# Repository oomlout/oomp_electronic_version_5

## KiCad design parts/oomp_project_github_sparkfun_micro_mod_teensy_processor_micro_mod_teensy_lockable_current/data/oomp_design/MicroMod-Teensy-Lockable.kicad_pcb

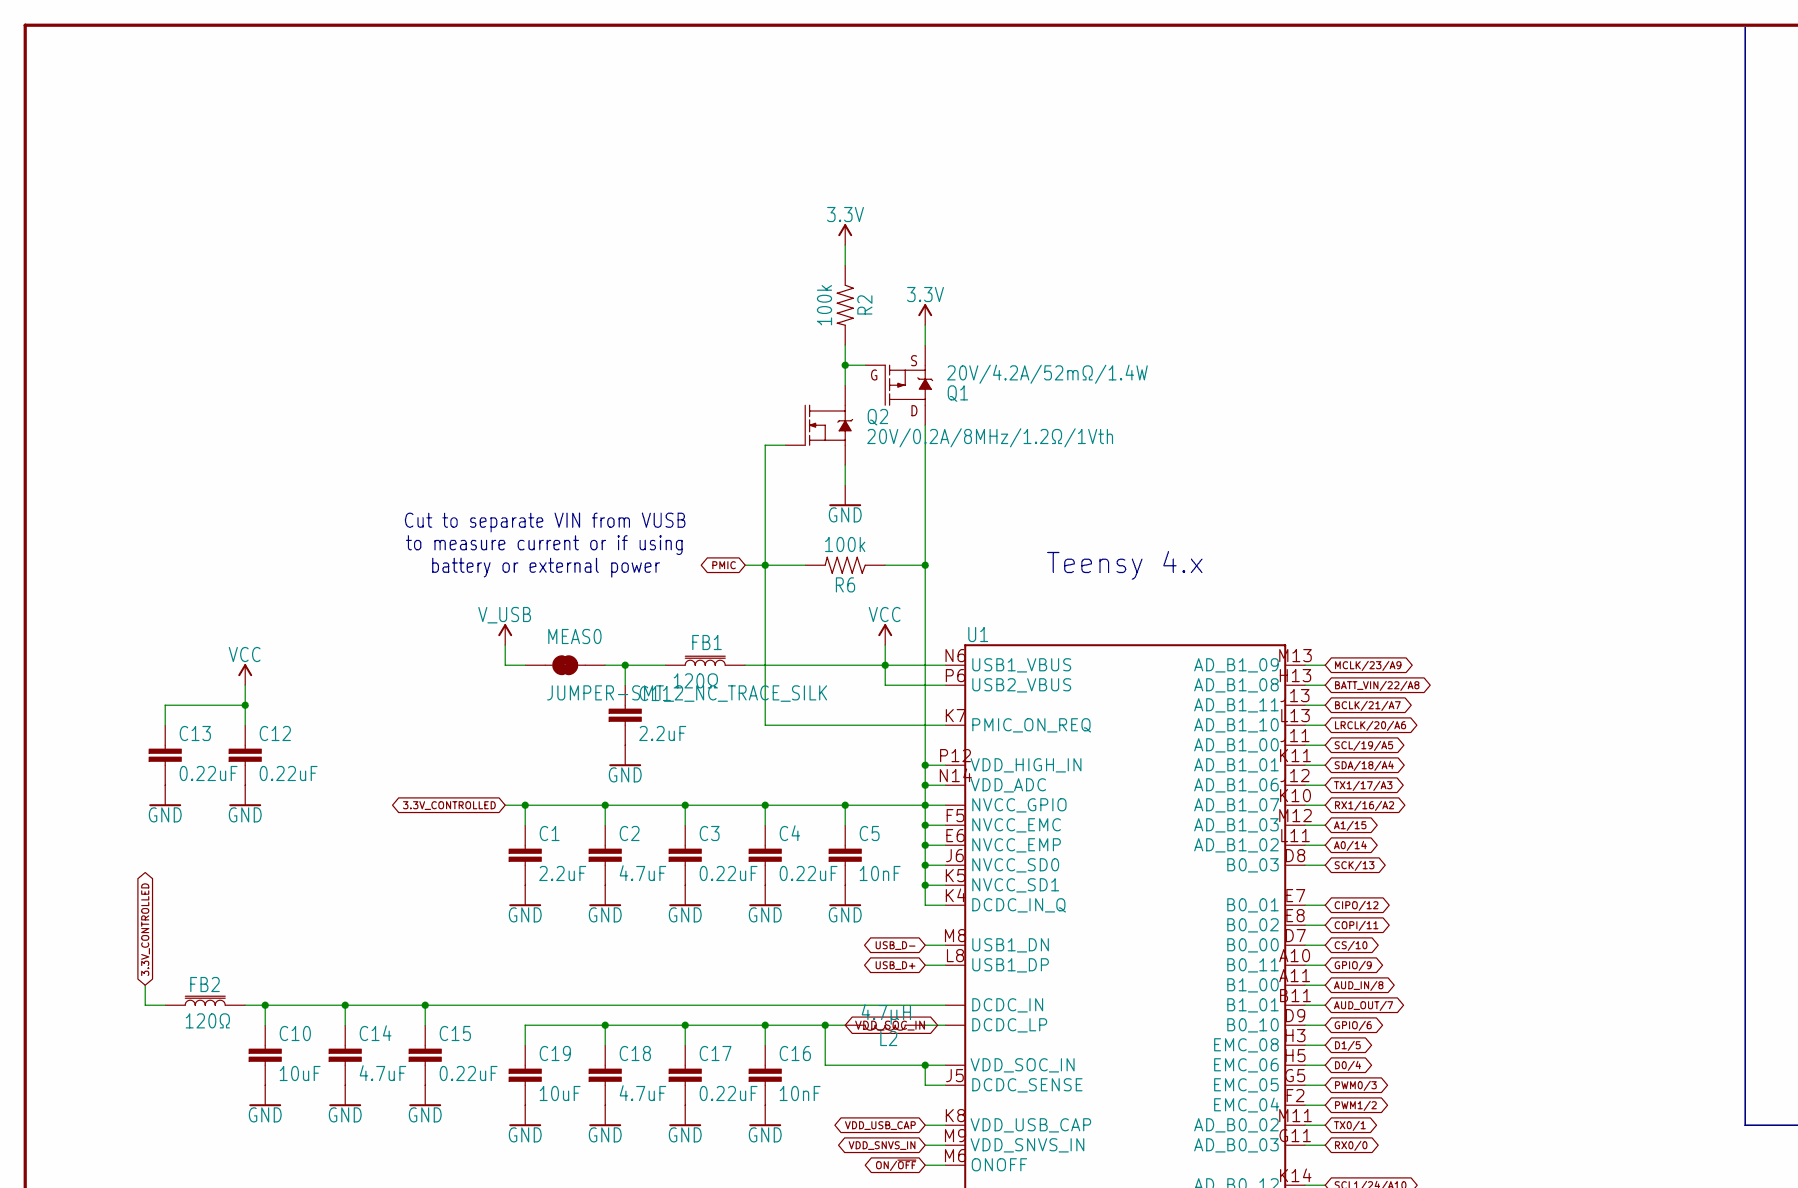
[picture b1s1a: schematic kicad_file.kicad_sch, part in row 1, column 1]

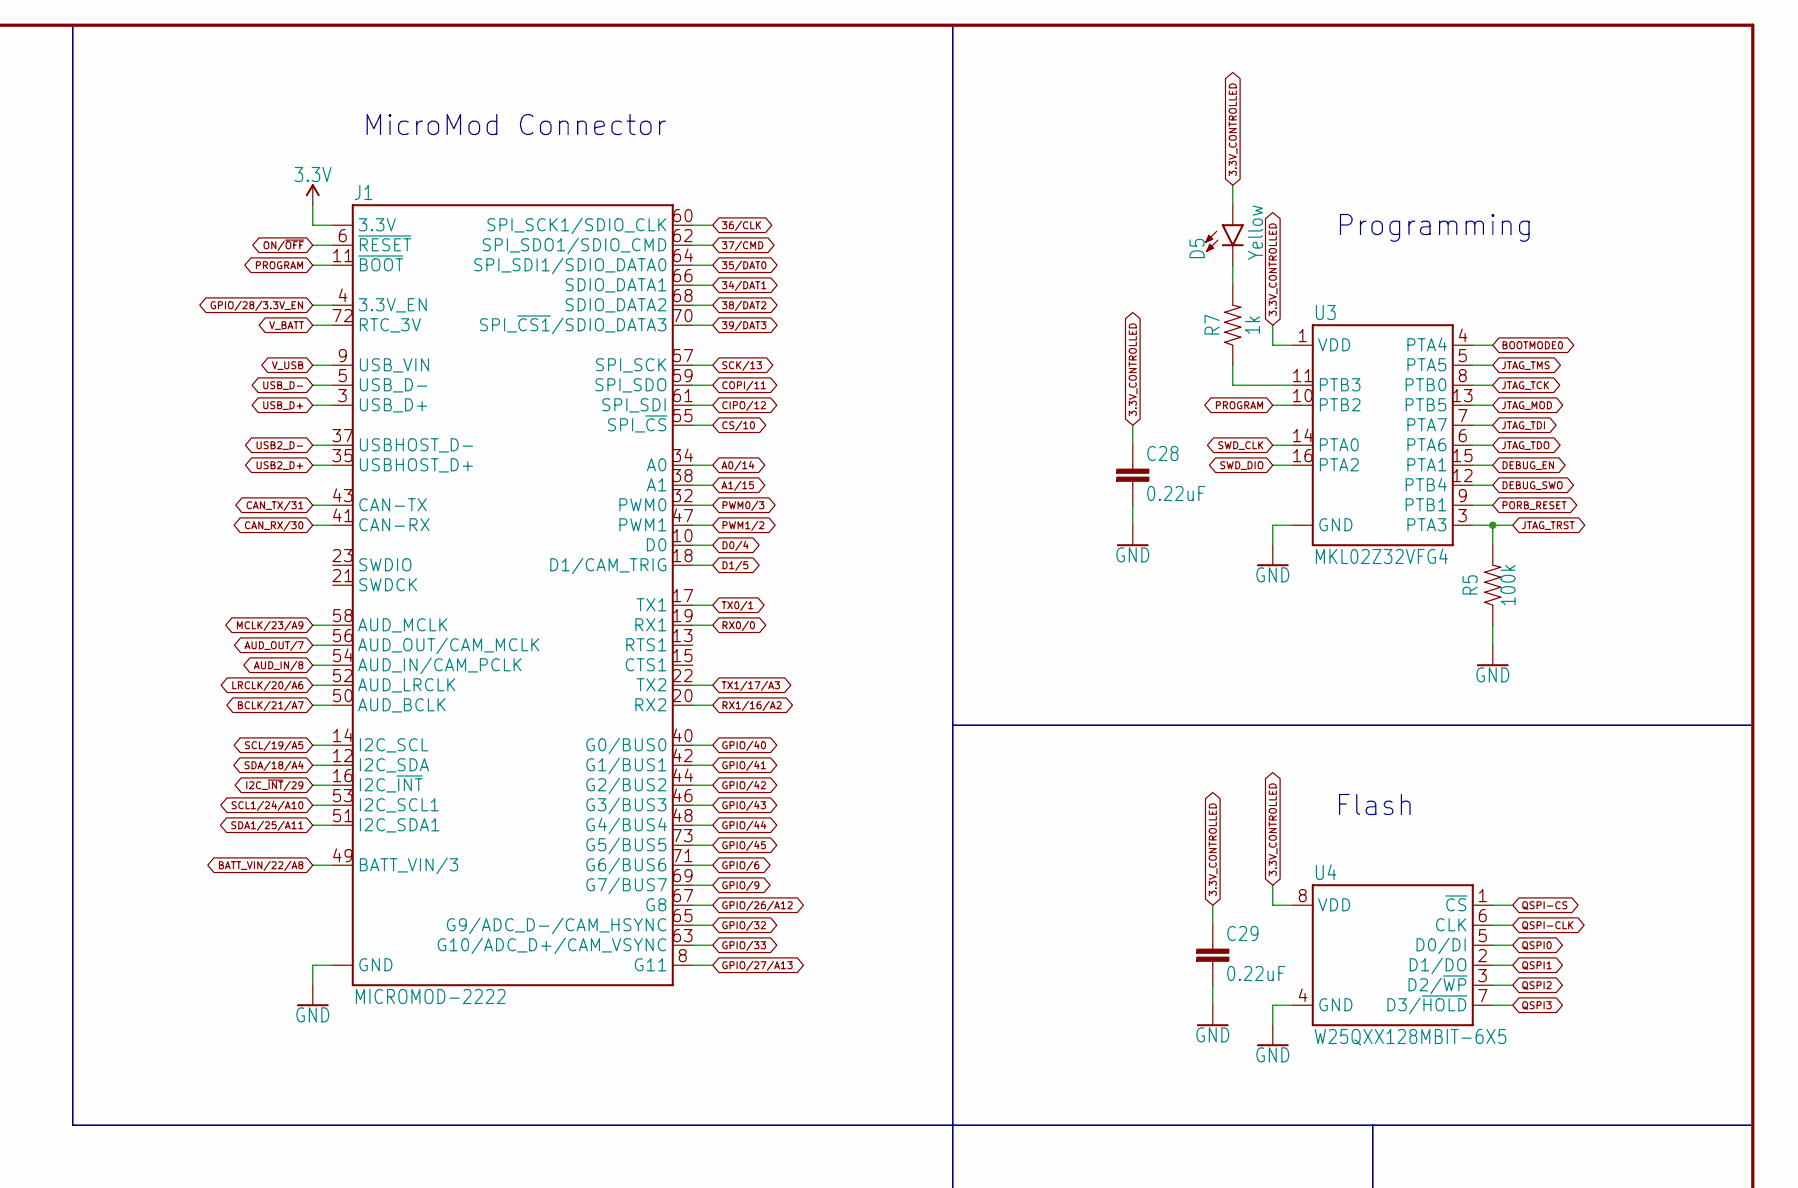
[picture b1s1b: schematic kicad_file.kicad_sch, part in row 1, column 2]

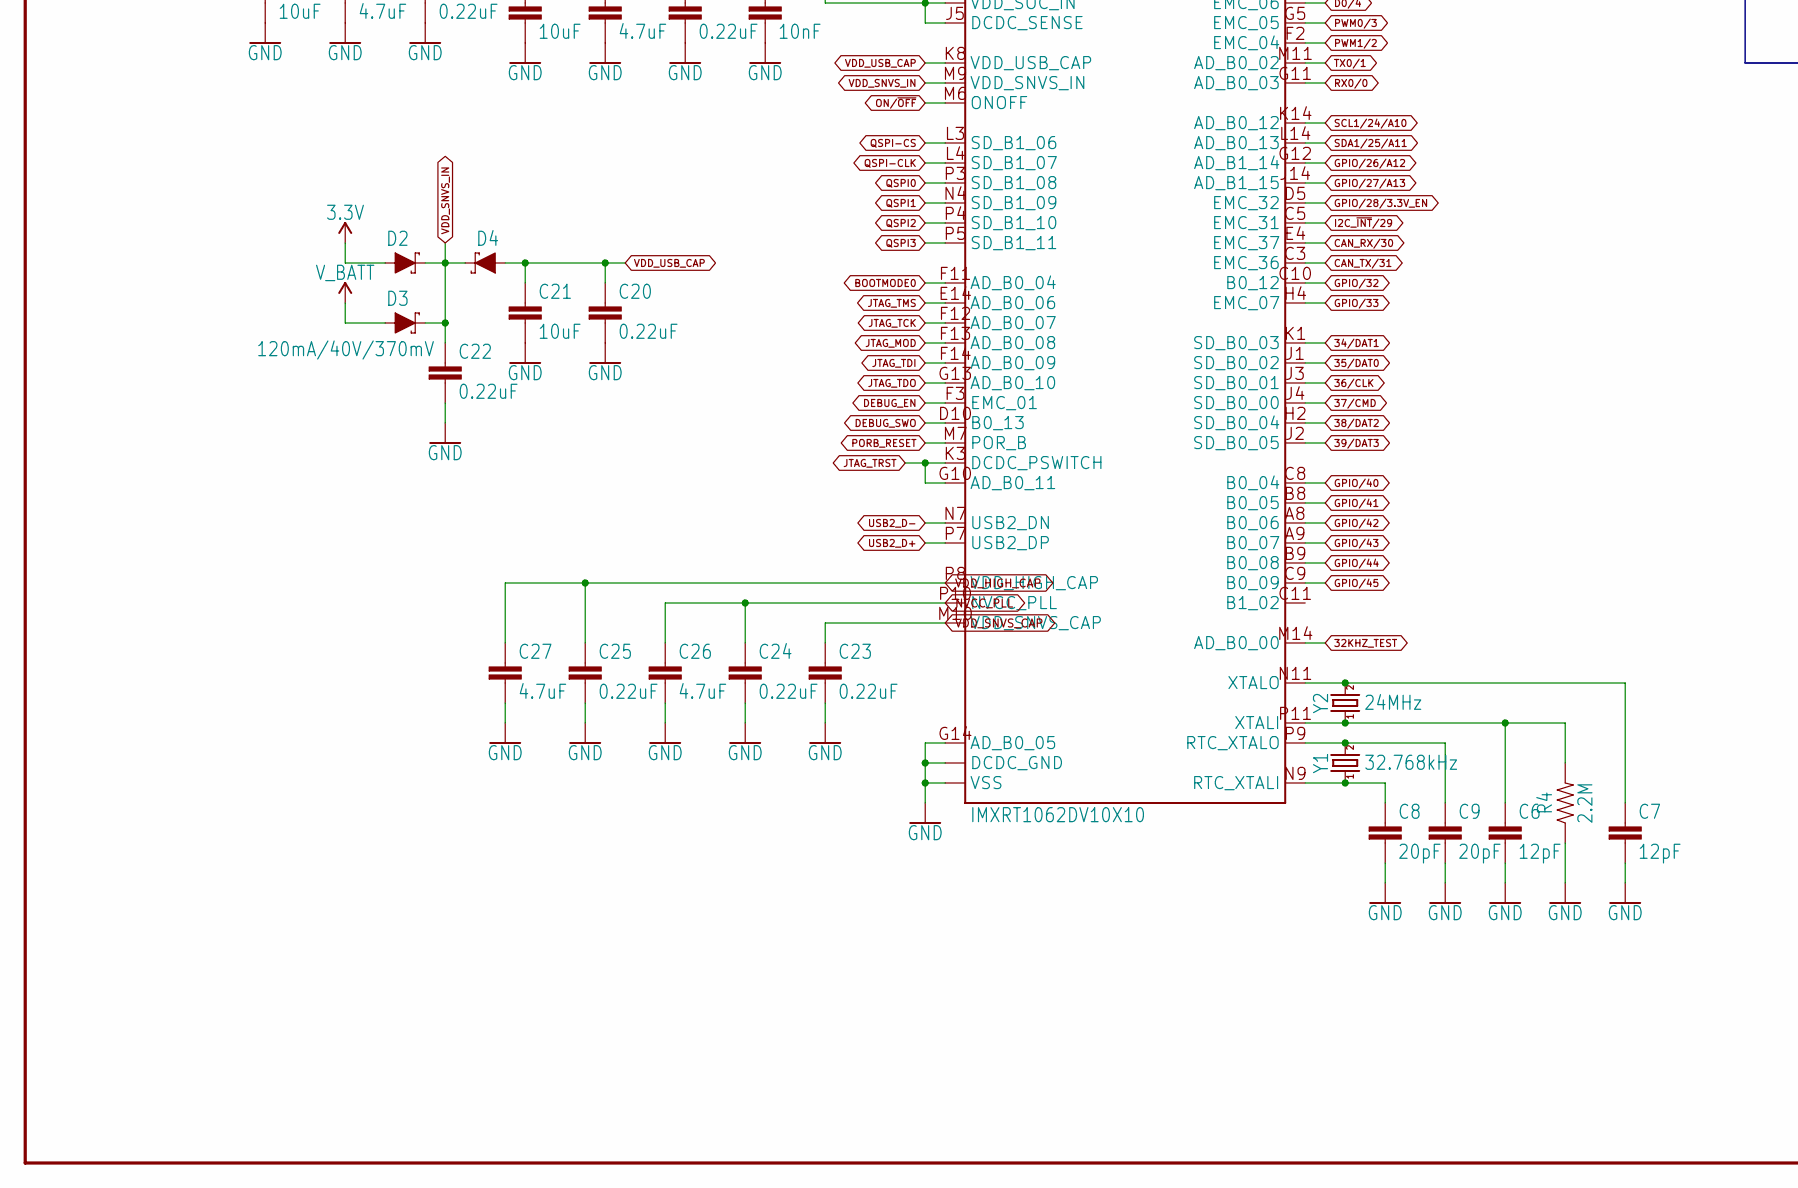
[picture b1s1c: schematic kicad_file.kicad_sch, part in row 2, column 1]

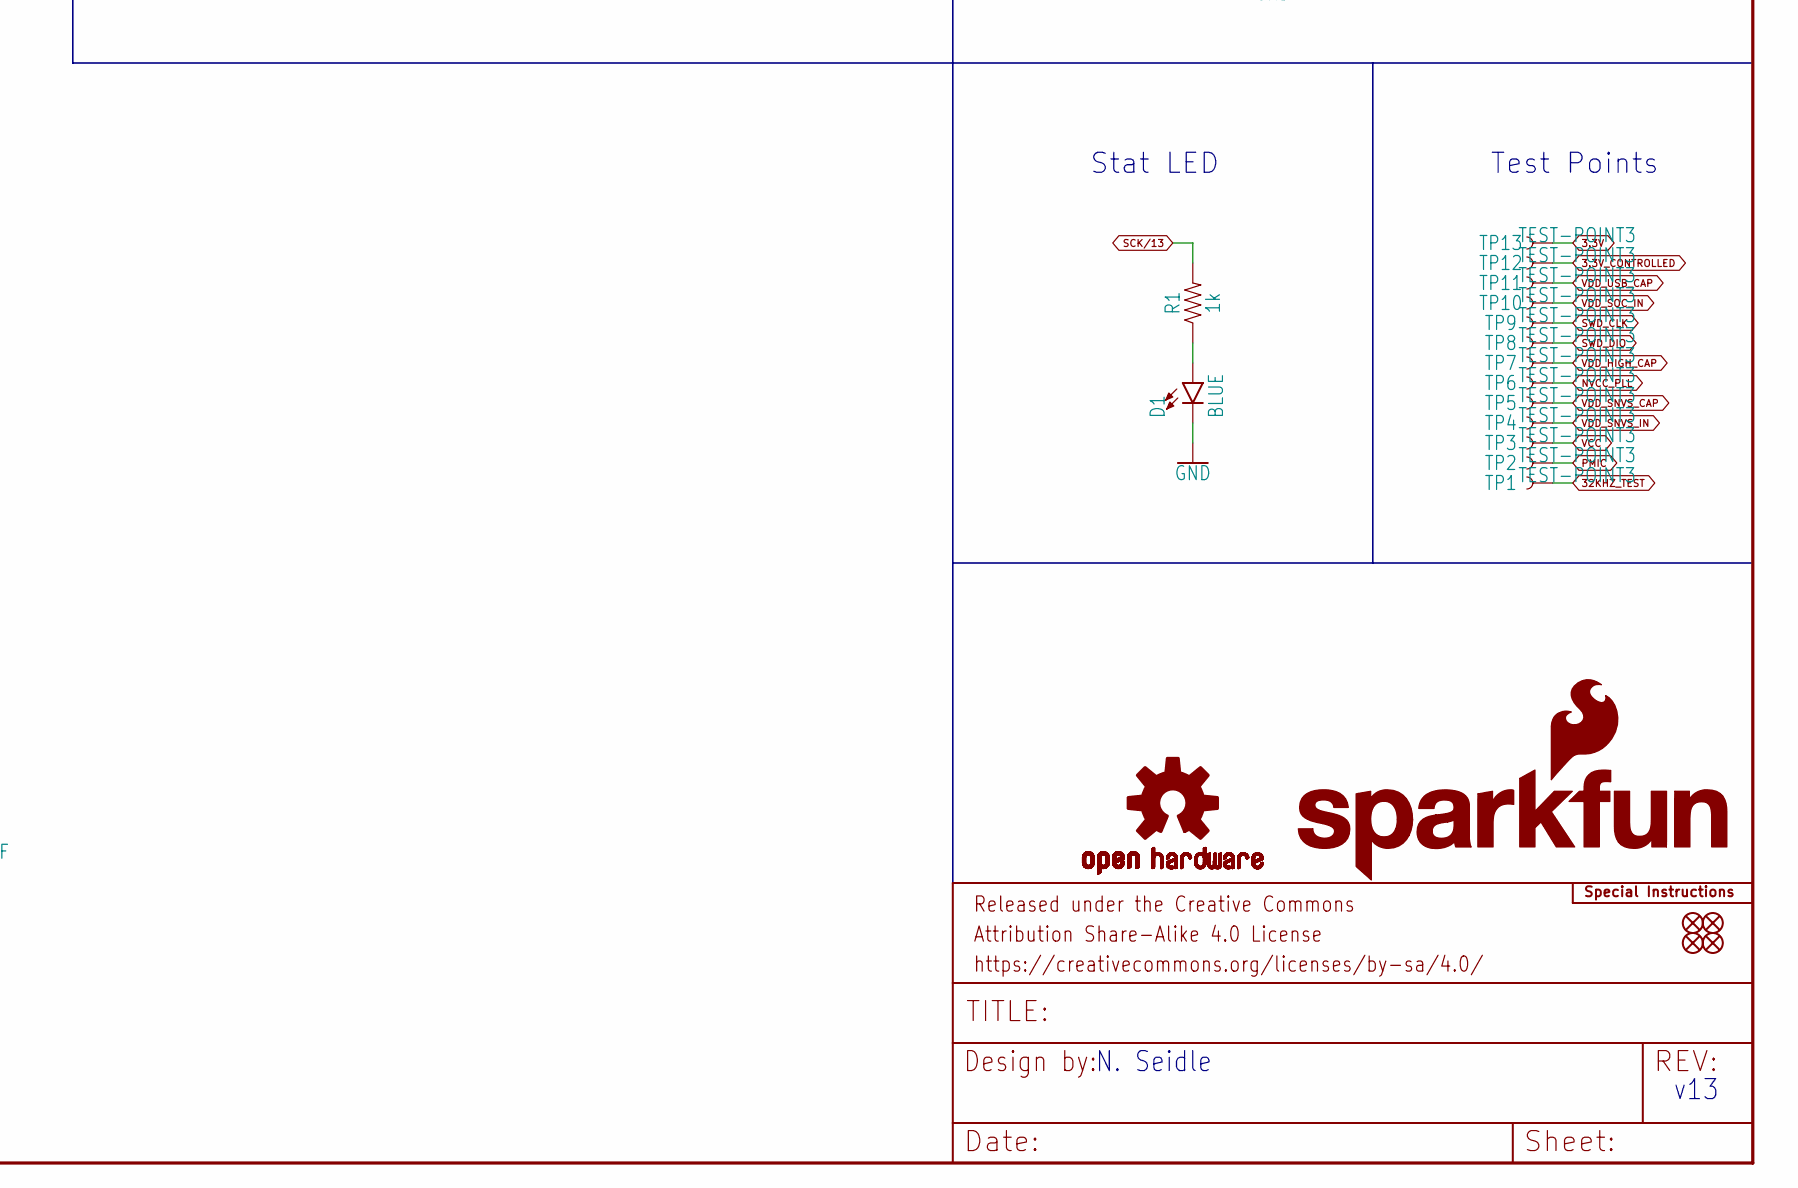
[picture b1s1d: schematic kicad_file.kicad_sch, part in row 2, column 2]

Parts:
C1, C11: 2.2uF; 0402-TIGHT
C2, C14, C18, C26, C27: 4.7uF; 0402-TIGHT
C3, C4, C12, C13, C15, C17, C20, C22, C23, C24, C25, C28, C29: 0.22uF; 0402-TIGHT
C5, C16: 10nF; 0402-TIGHT
C6, C7: 12pF; 0402-TIGHT
C8, C9: 20pF; 0402-TIGHT
C10, C19, C21: 10uF; 0402-TIGHT
D1: BLUE; LED-0603
D2, D3, D4: 120mA/40V/370mV; SOD-523
D5: Yellow; LED-0603
FB1, FB2: 120Ω; 0402-TIGHT
FD1, FD2, FD3, FD4: FIDUCIALUFIDUCIAL; FIDUCIAL-MICRO
FRAME1: FRAME-LEDGER; CREATIVE_COMMONS
J1: MICROMOD-2222; M.2-CARD-E-22
L2: 4.7μH; 1008(2520)
LOGO1: SFE_LOGO_NAME_FLAME.1_INCH; SFE_LOGO_NAME_FLAME_.1
LOGO2: OSHW-LOGONO_SILK; DUMMY
LOGO3: SPECIAL_INSTRUCTIONS-ORDERING; ORDERING_INSTRUCTIONS
MEAS0: JUMPER-SMT_2_NC_TRACE_SILK; SMT-JUMPER_2_NC_TRACE_SILK
Q1: 20V/4.2A/52mΩ/1.4W; SOT23-3
Q2: 20V/0.2A/8MHz/1.2Ω/1Vth; SOT-416FL
R1, R7: 1k; 0402-TIGHT
R2, R5, R6: 100k; 0402-TIGHT
R4: 2.2M; 0402-TIGHT
TP1, TP2, TP3, TP4, TP5, TP6, TP7, TP8, TP9, TP10, TP11, TP12, TP13: TEST-POINT3; PAD.03X.03
U1: IMXRT1062DV10X10; IMXRT1062
U3: MKL02Z32VFG4; QFN-16
U4: W25QXX128MBIT-6X5; WSON-8-6X5-SKINNY_CENTERPAD
Y1: 32.768kHz; CRYSTAL-SMD-3.2X1.5MM
Y2: 24MHz; CRYSTAL-SMD-2.0X1.6MM

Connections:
3.3V: D2.A, J1.2 (3.3V), J1.74 (3.3V), Q1.2 (S), R2.1, TP13.P$1
3.3V_CONTROLLED: C1.1, C2.1, C3.1, C4.1, C5.1, C28.1, C29.1, D5.A, FB2.1, Q1.3 (D), R6.1, TP12.P$1, U1.E6 (NVCC_EMP), U1.E9 (NVCC_GPIO), U1.F5 (NVCC_EMC), U1.F10 (NVCC_GPIO), U1.J6 (NVCC_SD0), U1.J10 (NVCC_GPIO), U1.K4 (DCDC_IN_Q), U1.K5 (NVCC_SD1), U1.N14 (VDD_ADC), U1.P12 (VDD_HIGH_IN), U3.1 (VDD), U4.8 (VDD)
24MHZ_1: C7.1, U1.N11 (XTALO), Y2.3 (2)
24MHZ_2: C6.1, R4.2, U1.P11 (XTALI), Y2.1
32KHZ_1: C8.1, U1.N9 (RTC_XTALI), Y1.P$1 (1)
32KHZ_2: C9.1, U1.P9 (RTC_XTALO), Y1.P$2 (2)
32KHZ_TEST: TP1.P$1, U1.M14 (AD_B0_00)
34/DAT1: J1.66 (SDIO_DATA1), U1.K1 (SD_B0_03)
35/DAT0: J1.64 (SPI_SDI1/SDIO_DATA0), U1.J1 (SD_B0_02)
36/CLK: J1.60 (SPI_SCK1/SDIO_CLK), U1.J3 (SD_B0_01)
37/CMD: J1.62 (SPI_SDO1/SDIO_CMD), U1.J4 (SD_B0_00)
38/DAT2: J1.68 (SDIO_DATA2), U1.H2 (SD_B0_04)
39/DAT3: J1.70 (SPI_~CS1/SDIO_DATA3), U1.J2 (SD_B0_05)
A0/14: J1.34 (A0), U1.L11 (AD_B1_02)
A1/15: J1.38 (A1), U1.M12 (AD_B1_03)
AUD_IN/8: J1.54 (AUD_IN/CAM_PCLK), U1.A11 (B1_00)
AUD_OUT/7: J1.56 (AUD_OUT/CAM_MCLK), U1.B11 (B1_01)
BATT_VIN/22/A8: J1.49 (BATT_VIN/3), U1.H13 (AD_B1_08)
BCLK/21/A7: J1.50 (AUD_BCLK), U1.J13 (AD_B1_11)
BOOTMODE0: U1.F11 (AD_B0_04), U3.4 (PTA4)
CAN_RX/30: J1.41 (CAN-RX), U1.E4 (EMC_37)
CAN_TX/31: J1.43 (CAN-TX), U1.C3 (EMC_36)
CIPO/12: J1.61 (SPI_SDI), U1.E7 (B0_01)
COPI/11: J1.59 (SPI_SDO), U1.E8 (B0_02)
CS/10: J1.55 (SPI_~CS), U1.D7 (B0_00)
D0/4: J1.10 (D0), U1.H5 (EMC_06)
D1/5: J1.18 (D1/CAM_TRIG), U1.H3 (EMC_08)
DCDC_IN: C10.1, C14.1, C15.1, FB2.2, U1.L1 (DCDC_IN), U1.L2 (DCDC_IN)
DCDC_LP: L2.1, U1.M1 (DCDC_LP), U1.M2 (DCDC_LP)
DEBUG_EN: U1.F3 (EMC_01), U3.15 (PTA1)
DEBUG_SWO: U1.D10 (B0_13), U3.12 (PTB4)
GND: C1.2, C2.2, C3.2, C4.2, C5.2, C6.2, C7.2, C8.2, C9.2, C10.2, C11.2, C12.2, C13.2, C14.2, C15.2, C16.2, C17.2, C18.2, C19.2, C20.2, C21.2, C22.2, C23.2, C24.2, C25.2, C26.2, C27.2, C28.2, C29.2, D1.C, J1.1 (GND), J1.7 (GND), J1.33 (GND), J1.36 (GND), J1.39 (GND), J1.45 (GND), J1.75 (GND), J1.GND1 (GND), J1.GND2 (GND), J1.GND3 (GND), Q2.2 (S), R4.1, R5.1, U1.A1 (VSS), U1.A14 (VSS), U1.B5 (VSS), U1.B10 (VSS), U1.E2 (VSS), U1.E13 (VSS), U1.G7 (VSS), U1.G8 (VSS), U1.G14 (AD_B0_05), U1.H7 (VSS), U1.H8 (VSS), U1.J7 (VSS), U1.J8 (VSS), U1.K2 (VSS), U1.K6 (VSS), U1.K9 (VSS), U1.K13 (VSS), U1.L9 (VSS), U1.N1 (DCDC_GND), U1.N2 (DCDC_GND), U1.N5 (VSS), U1.N8 (VSS), U1.P1 (VSS), U1.P14 (VSS), U3.2 (GND), U3.17 (GND), U4.4 (GND)
GPIO/6: J1.71 (G6/BUS6), U1.D9 (B0_10)
GPIO/9: J1.69 (G7/BUS7), U1.A10 (B0_11)
GPIO/26/A12: J1.67 (G8), U1.G12 (AD_B1_14)
GPIO/27/A13: J1.8 (G11), U1.J14 (AD_B1_15)
GPIO/28/3.3V_EN: J1.4 (3.3V_EN), U1.D5 (EMC_32)
GPIO/32: J1.65 (G9/ADC_D-/CAM_HSYNC), U1.C10 (B0_12)
GPIO/33: J1.63 (G10/ADC_D+/CAM_VSYNC), U1.H4 (EMC_07)
GPIO/40: J1.40 (G0/BUS0), U1.C8 (B0_04)
GPIO/41: J1.42 (G1/BUS1), U1.B8 (B0_05)
GPIO/42: J1.44 (G2/BUS2), U1.A8 (B0_06)
GPIO/43: J1.46 (G3/BUS3), U1.A9 (B0_07)
GPIO/44: J1.48 (G4/BUS4), U1.B9 (B0_08)
GPIO/45: J1.73 (G5/BUS5), U1.C9 (B0_09)
I2C_~INT/29: J1.16 (I2C_~INT), U1.C5 (EMC_31)
JTAG_MOD: U1.F13 (AD_B0_08), U3.13 (PTB5)
JTAG_TCK: U1.F12 (AD_B0_07), U3.8 (PTB0)
JTAG_TDI: U1.F14 (AD_B0_09), U3.7 (PTA7)
JTAG_TDO: U1.G13 (AD_B0_10), U3.6 (PTA6)
JTAG_TMS: U1.E14 (AD_B0_06), U3.5 (PTA5)
JTAG_TRST: R5.2, U1.G10 (AD_B0_11), U1.K3 (DCDC_PSWITCH), U3.3 (PTA3)
LRCLK/20/A6: J1.52 (AUD_LRCLK), U1.L13 (AD_B1_10)
MCLK/23/A9: J1.58 (AUD_MCLK), U1.M13 (AD_B1_09)
unnamed: D1.A, R1.1
unnamed: Q1.1 (G), Q2.3 (D), R2.2
unnamed: C11.1, FB1.1, MEAS0.2
unnamed: R7.1, U3.11 (PTB3)
unnamed: D5.C, R7.2
NVCC_PLL: C24.1, C26.1, TP6.P$1, U1.P10 (NVCC_PLL)
ON/~OFF: J1.6 (~RESET), U1.M6 (ONOFF)
PMIC: Q2.1 (G), R6.2, TP2.P$1, U1.K7 (PMIC_ON_REQ)
PORB_RESET: U1.M7 (POR_B), U3.9 (PTB1)
PROGRAM: J1.11 (~BOOT), U3.10 (PTB2)
PWM0/3: J1.32 (PWM0), U1.G5 (EMC_05)
PWM1/2: J1.47 (PWM1), U1.F2 (EMC_04)
QSPI0: U1.P3 (SD_B1_08), U4.5 (D0/DI)
QSPI1: U1.N4 (SD_B1_09), U4.2 (D1/DO)
QSPI2: U1.P4 (SD_B1_10), U4.3 (D2/~WP)
QSPI3: U1.P5 (SD_B1_11), U4.7 (D3/~HOLD)
QSPI-CLK: U1.L4 (SD_B1_07), U4.6 (CLK)
QSPI-CS: U1.L3 (SD_B1_06), U4.1 (~CS)
RX0/0: J1.19 (RX1), U1.G11 (AD_B0_03)
RX1/16/A2: J1.20 (RX2), U1.K10 (AD_B1_07)
SCK/13: J1.57 (SPI_SCK), R1.2, U1.D8 (B0_03)
SCL1/24/A10: J1.53 (I2C_SCL1), U1.K14 (AD_B0_12)
SCL/19/A5: J1.14 (I2C_SCL), U1.J11 (AD_B1_00)
SDA1/25/A11: J1.51 (I2C_SDA1), U1.L14 (AD_B0_13)
SDA/18/A4: J1.12 (I2C_SDA), U1.K11 (AD_B1_01)
SWD_CLK: TP9.P$1, U3.14 (PTA0)
SWD_DIO: TP8.P$1, U3.16 (PTA2)
TX0/1: J1.17 (TX1), U1.M11 (AD_B0_02)
TX1/17/A3: J1.22 (TX2), U1.J12 (AD_B1_06)
USB2_D+: J1.35 (USBHOST_D+), U1.P7 (USB2_DP)
USB2_D-: J1.37 (USBHOST_D-), U1.N7 (USB2_DN)
USB_D+: J1.3 (USB_D+), U1.L8 (USB1_DP)
USB_D-: J1.5 (USB_D-), U1.M8 (USB1_DN)
VCC: C12.1, C13.1, FB1.2, TP3.P$1, U1.N6 (USB1_VBUS), U1.P6 (USB2_VBUS)
VDD_HIGH_CAP: C25.1, C27.1, TP7.P$1, U1.P8 (VDD_HIGH_CAP)
VDD_SNVS_CAP: C23.1, TP5.P$1, U1.M10 (VDD_SNVS_CAP)
VDD_SNVS_IN: C22.1, D2.C, D3.C, D4.C, TP4.P$1, U1.M9 (VDD_SNVS_IN)
VDD_SOC_IN: C16.1, C17.1, C18.1, C19.1, L2.2, TP10.P$1, U1.F6 (VDD_SOC_IN), U1.F7 (VDD_SOC_IN), U1.F8 (VDD_SOC_IN), U1.F9 (VDD_SOC_IN), U1.G6 (VDD_SOC_IN), U1.G9 (VDD_SOC_IN), U1.H6 (VDD_SOC_IN), U1.H9 (VDD_SOC_IN), U1.J5 (DCDC_SENSE), U1.J9 (VDD_SOC_IN)
VDD_USB_CAP: C20.1, C21.1, D4.A, TP11.P$1, U1.K8 (VDD_USB_CAP)
V_BATT: D3.A, J1.72 (RTC_3V)
V_USB: J1.9 (USB_VIN), MEAS0.1

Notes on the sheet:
Flash
N. Seidle
Teensy 4.x
Test Points
v13
Stat LED
Cut to separate VIN from VUSB to measure current or if using battery or external power
MicroMod Connector
Programming

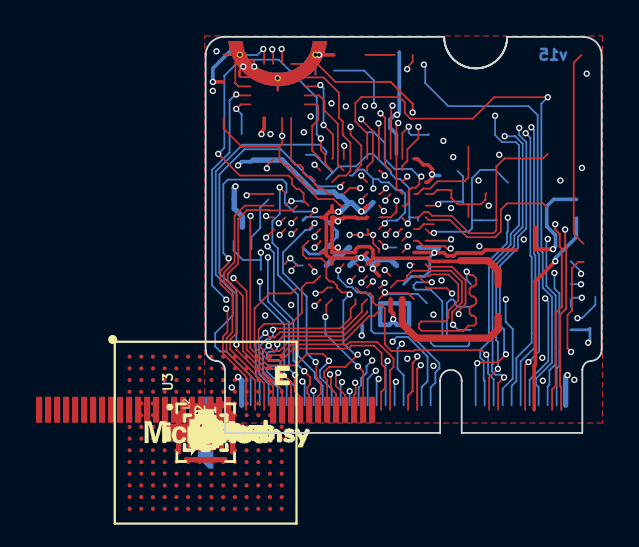
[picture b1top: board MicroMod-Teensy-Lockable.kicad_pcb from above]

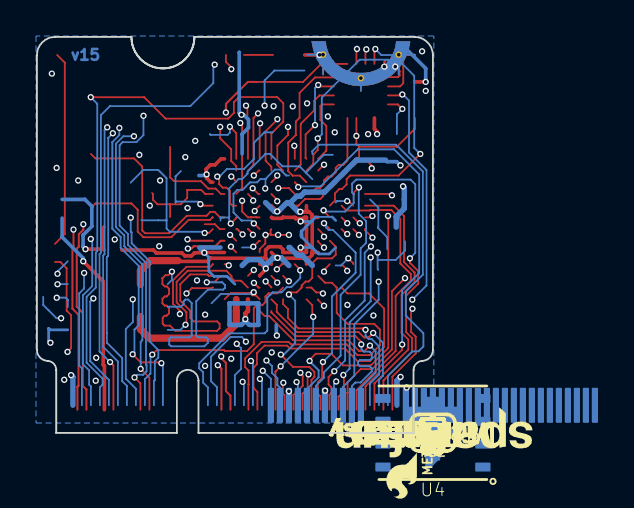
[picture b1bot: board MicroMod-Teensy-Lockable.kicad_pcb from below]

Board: 4 copper layers, 22.0 x 22.0 mm, 84 parts (53 on the bottom side), 95 nets.

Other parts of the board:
U$1, U$3: TEENSY2
U$4: MICROMOD_MI_LOGO_.35
U$6: SFE_LOGO_FLAME_.1
U$7, U$11: MICROMOD_LOGO_.3
U$8: MEAS2
U$9: PROG0
U$10: STAT1
U$16, U$17: LOCKED4#PNG

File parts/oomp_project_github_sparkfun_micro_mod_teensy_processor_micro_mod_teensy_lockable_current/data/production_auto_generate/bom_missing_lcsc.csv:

Designator,Comment,Footprint,OOMP ID,Reason
C3,0.22uF,MicroMod-Teensy-Lockable-import-fps:0402-TIGHT,,No verified LCSC part number
C4,0.22uF,MicroMod-Teensy-Lockable-import-fps:0402-TIGHT,,No verified LCSC part number
C6,12pF,MicroMod-Teensy-Lockable-import-fps:0402-TIGHT,,No verified LCSC part number
C7,12pF,MicroMod-Teensy-Lockable-import-fps:0402-TIGHT,,No verified LCSC part number
C8,20pF,MicroMod-Teensy-Lockable-import-fps:0402-TIGHT,,No verified LCSC part number
C9,20pF,MicroMod-Teensy-Lockable-import-fps:0402-TIGHT,,No verified LCSC part number
C12,0.22uF,MicroMod-Teensy-Lockable-import-fps:0402-TIGHT,,No verified LCSC part number
C13,0.22uF,MicroMod-Teensy-Lockable-import-fps:0402-TIGHT,,No verified LCSC part number
C15,0.22uF,MicroMod-Teensy-Lockable-import-fps:0402-TIGHT,,No verified LCSC part number
C17,0.22uF,MicroMod-Teensy-Lockable-import-fps:0402-TIGHT,,No verified LCSC part number
C20,0.22uF,MicroMod-Teensy-Lockable-import-fps:0402-TIGHT,,No verified LCSC part number
C22,0.22uF,MicroMod-Teensy-Lockable-import-fps:0402-TIGHT,,No verified LCSC part number
C23,0.22uF,MicroMod-Teensy-Lockable-import-fps:0402-TIGHT,,No verified LCSC part number
C24,0.22uF,MicroMod-Teensy-Lockable-import-fps:0402-TIGHT,,No verified LCSC part number
C25,0.22uF,MicroMod-Teensy-Lockable-import-fps:0402-TIGHT,,No verified LCSC part number
C28,0.22uF,MicroMod-Teensy-Lockable-import-fps:0402-TIGHT,,No verified LCSC part number
C29,0.22uF,MicroMod-Teensy-Lockable-import-fps:0402-TIGHT,,No verified LCSC part number
D1,BLUE,MicroMod-Teensy-Lockable-import-fps:LED-0603,electronic_led_0603_blue,No verified LCSC part number
D2,120mA/40V/370mV,MicroMod-Teensy-Lockable-import-fps:SOD-523,,No verified LCSC part number
D3,120mA/40V/370mV,MicroMod-Teensy-Lockable-import-fps:SOD-523,,No verified LCSC part number
D4,120mA/40V/370mV,MicroMod-Teensy-Lockable-import-fps:SOD-523,,No verified LCSC part number
D5,Yellow,MicroMod-Teensy-Lockable-import-fps:LED-0603,electronic_led_0603_yellow,No verified LCSC part number
FB1,120Ω,MicroMod-Teensy-Lockable-import-fps:0402-TIGHT,,No verified LCSC part number
FB2,120Ω,MicroMod-Teensy-Lockable-import-fps:0402-TIGHT,,No verified LCSC part number
FD1,FIDUCIALUFIDUCIAL,MicroMod-Teensy-Lockable-import-fps:FIDUCIAL-MICRO,,No verified LCSC part number
FD2,FIDUCIALUFIDUCIAL,MicroMod-Teensy-Lockable-import-fps:FIDUCIAL-MICRO,,No verified LCSC part number
FD3,FIDUCIALUFIDUCIAL,MicroMod-Teensy-Lockable-import-fps:FIDUCIAL-MICRO,,No verified LCSC part number
FD4,FIDUCIALUFIDUCIAL,MicroMod-Teensy-Lockable-import-fps:FIDUCIAL-MICRO,,No verified LCSC part number
FRAME1,FRAME-LEDGER,MicroMod-Teensy-Lockable-import-fps:CREATIVE_COMMONS,,No verified LCSC part number
J1,MICROMOD-2222,MicroMod-Teensy-Lockable-import-fps:M.2-CARD-E-22,,No verified LCSC part number
L2,4.7μH,MicroMod-Teensy-Lockable-import-fps:1008(2520),,No verified LCSC part number
MEAS0,,MicroMod-Teensy-Lockable-import-fps:SMT-JUMPER_2_NC_TRACE_SILK,,No verified LCSC part number
Q1,20V/4.2A/52mΩ/1.4W,MicroMod-Teensy-Lockable-import-fps:SOT23-3,,No verified LCSC part number
Q2,20V/0.2A/8MHz/1.2Ω/1Vth,MicroMod-Teensy-Lockable-import-fps:SOT-416FL,,No verified LCSC part number
TP1,,MicroMod-Teensy-Lockable-import-fps:PAD.03X.03,,No verified LCSC part number
TP2,,MicroMod-Teensy-Lockable-import-fps:PAD.03X.03,,No verified LCSC part number
TP3,,MicroMod-Teensy-Lockable-import-fps:PAD.03X.03,,No verified LCSC part number
TP4,,MicroMod-Teensy-Lockable-import-fps:PAD.03X.03,,No verified LCSC part number
TP5,,MicroMod-Teensy-Lockable-import-fps:PAD.03X.03,,No verified LCSC part number
TP6,,MicroMod-Teensy-Lockable-import-fps:PAD.03X.03,,No verified LCSC part number
TP7,,MicroMod-Teensy-Lockable-import-fps:PAD.03X.03,,No verified LCSC part number
TP8,,MicroMod-Teensy-Lockable-import-fps:PAD.03X.03,,No verified LCSC part number
TP9,,MicroMod-Teensy-Lockable-import-fps:PAD.03X.03,,No verified LCSC part number
TP10,,MicroMod-Teensy-Lockable-import-fps:PAD.03X.03,,No verified LCSC part number
TP11,,MicroMod-Teensy-Lockable-import-fps:PAD.03X.03,,No verified LCSC part number
TP12,,MicroMod-Teensy-Lockable-import-fps:PAD.03X.03,,No verified LCSC part number
TP13,,MicroMod-Teensy-Lockable-import-fps:PAD.03X.03,,No verified LCSC part number
U1,IMXRT1062DV10X10,MicroMod-Teensy-Lockable-import-fps:IMXRT1062,,No verified LCSC part number
U3,MKL02Z32VFG4,MicroMod-Teensy-Lockable-import-fps:QFN-16,,No verified LCSC part number
U4,W25QXX128MBIT-6X5,MicroMod-Teensy-Lockable-import-fps:WSON-8-6X5-SKINNY_CENTERPAD,,No verified LCSC part number
U$1,,MicroMod-Teensy-Lockable-import-fps:TEENSY2,,No verified LCSC part number
U$3,,MicroMod-Teensy-Lockable-import-fps:TEENSY2,,No verified LCSC part number
U$4,,MicroMod-Teensy-Lockable-import-fps:MICROMOD_MI_LOGO_.35,,No verified LCSC part number
U$6,,MicroMod-Teensy-Lockable-import-fps:SFE_LOGO_FLAME_.1,,No verified LCSC part number
U$7,,MicroMod-Teensy-Lockable-import-fps:MICROMOD_LOGO_.3,,No verified LCSC part number
U$8,,MicroMod-Teensy-Lockable-import-fps:MEAS2,,No verified LCSC part number
U$9,,MicroMod-Teensy-Lockable-import-fps:PROG0,,No verified LCSC part number
U$10,,MicroMod-Teensy-Lockable-import-fps:STAT1,,No verified LCSC part number
U$11,,MicroMod-Teensy-Lockable-import-fps:MICROMOD_LOGO_.3,,No verified LCSC part number
U$16,,MicroMod-Teensy-Lockable-import-fps:LOCKED4#PNG,,No verified LCSC part number
U$17,,MicroMod-Teensy-Lockable-import-fps:LOCKED4#PNG,,No verified LCSC part number
Y2,24MHz,MicroMod-Teensy-Lockable-import-fps:CRYSTAL-SMD-2.0X1.6MM,,No verified LCSC part number

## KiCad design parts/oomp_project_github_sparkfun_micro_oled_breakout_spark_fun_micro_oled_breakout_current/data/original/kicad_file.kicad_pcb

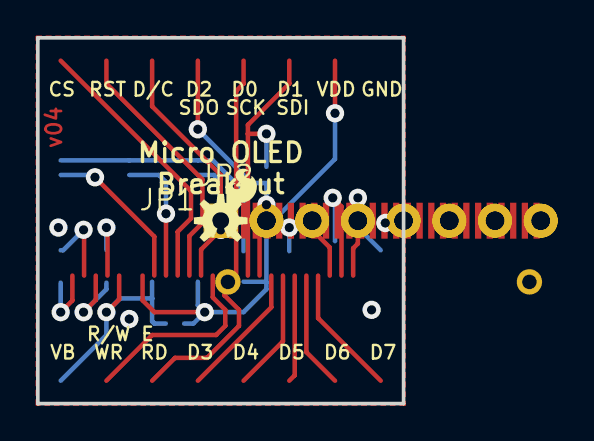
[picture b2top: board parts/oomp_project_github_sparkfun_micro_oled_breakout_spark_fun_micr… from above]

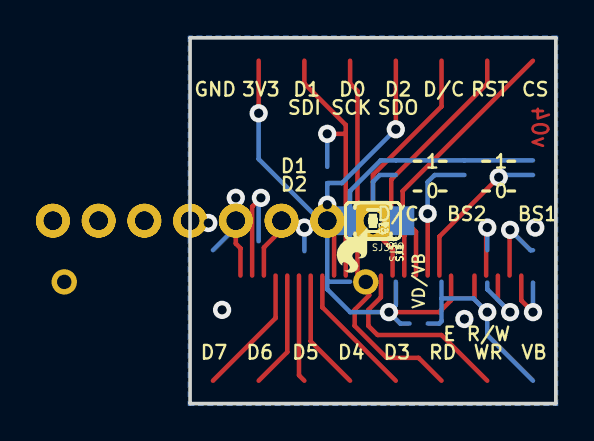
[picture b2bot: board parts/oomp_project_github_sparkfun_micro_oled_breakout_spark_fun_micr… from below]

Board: 2 copper layers, 20.3 x 20.3 mm, 24 parts (17 on the bottom side), 26 nets.

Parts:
C1: 2.2uF; 0805
C2, C3: 1uF X5R; 0805
C4, C6: 1uF; 0603-CAP
C5: 4.7uF/16V; 1206
FID1, FID2: FIDUCIAL1X2; FIDUCIAL-1X2
FRAME1: FRAME-LETTER; CREATIVE_COMMONS
JP1, JP2: 1X08_PIN1_NO_SILK
LOGO2, LOGO4: SFE_LOGO_FLAME.1_INCH; SFE_LOGO_FLAME_.1
LOGO3: OSHW-LOGOS; OSHW-LOGO-S
OLED1: OLED0.66; OLED-0.66-64X48
R1: 390k; 0603-RES
R2: 10k; 0603-RES
SJ1: BS1; PAD-JUMPER-3-2OF3_NC_BY_PASTE_YES_SILK_FULL_BOX
SJ2: BS2; PAD-JUMPER-3-2OF3_NC_BY_PASTE_YES_SILK_FULL_BOX
SJ3: PAD-JUMPER-2-NC_BY_TRACE_NO_SILK
SJ4: PAD-JUMPER-3-NO-TIGHT
SJ5: PAD-JUMPER-2-NO_YES_SILK
TP1, TP2: TEST-POINT3X5; PAD.03X.05

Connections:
BS1: OLED1.9, SJ1.2
BS2: OLED1.10, SJ2.2
C1N: C2.2, OLED1.5
C1P: C2.1, OLED1.4
C2N: C3.2, OLED1.3
C2P: C3.1, OLED1.2
CS: JP1.8, OLED1.11
D0/SCK: JP1.4, OLED1.16
D1/MOSI: JP1.3, OLED1.17, SJ5.1
D2: JP1.5, OLED1.18, SJ5.2
D3: JP2.4, OLED1.19
D4: JP2.5, OLED1.20
D5: JP2.6, OLED1.21
D6: JP2.7, OLED1.22
D7: JP2.8, OLED1.23
D/C: JP1.6, OLED1.13, SJ4.2
GND: C1.2, C4.2, C5.2, C6.2, JP1.1, OLED1.1, OLED1.7, OLED1.27, OLED1.28, R1.1, SJ1.3, SJ2.3, SJ4.3
IREF: OLED1.24, R1.2
RD/E: JP2.3, OLED1.15
RESET: JP1.7, OLED1.12
VBAT: C6.1, JP2.1, OLED1.6, SJ3.1
VCC: C1.1, OLED1.26, TP1.P$1, TP2.P$1
VCOMH: C5.1, OLED1.25
VDD: C4.1, JP1.2, OLED1.8, R2.2, SJ3.2
VDD_PU: R2.1, SJ1.1, SJ2.1, SJ4.1
WR/RW: JP2.2, OLED1.14

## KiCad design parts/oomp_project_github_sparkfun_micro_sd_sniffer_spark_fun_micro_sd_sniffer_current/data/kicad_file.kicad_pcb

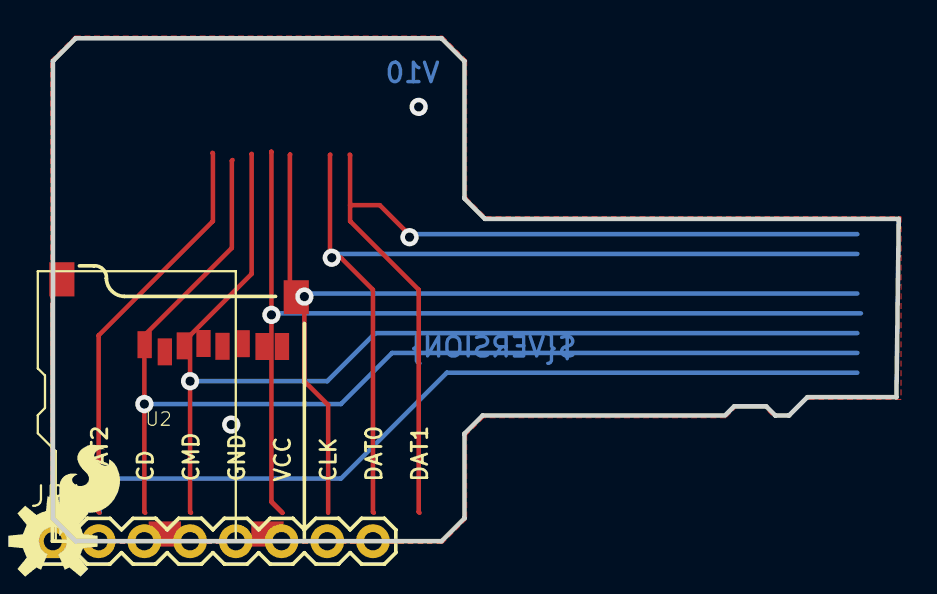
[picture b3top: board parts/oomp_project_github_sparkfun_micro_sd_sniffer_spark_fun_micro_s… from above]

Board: 16 copper layers, 47.0 x 27.9 mm, 9 parts (1 on the bottom side), 8 nets.

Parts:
FID1, FID2: FIDUCIAL1X2; FIDUCIAL-1X2
FRAME1: CREATIVE_COMMONS
JP1: 1X08
LOGO1: OSHW-LOGOM; OSHW-LOGO-M
LOGO2: SFE_LOGO_FLAME.2_INCH; SFE_LOGO_FLAME_.2
LOGO3: SFE_LOGO_NAME_FLAME.1_INCH; SFE_LOGO_NAME_FLAME_.1
U1: MICRO-SDCARD
U2: microSD Socket; MICROSD_1_1

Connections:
CD/DAT3: JP1.2, U1.CD/DAT3, U2.2
CLK: JP1.6, U1.CLK, U2.5
CMD: JP1.3, U1.CMD, U2.3
DAT0: JP1.7, U1.DAT0, U2.7
DAT1: JP1.8, U1.DAT1, U2.8
DAT2: JP1.1, U1.DAT2, U2.1
GND: JP1.4, U1.GND, U2.6, U2.CD1, U2.CD2, U2.GND1, U2.GND3
VCC: JP1.5, U1.VCC, U2.4

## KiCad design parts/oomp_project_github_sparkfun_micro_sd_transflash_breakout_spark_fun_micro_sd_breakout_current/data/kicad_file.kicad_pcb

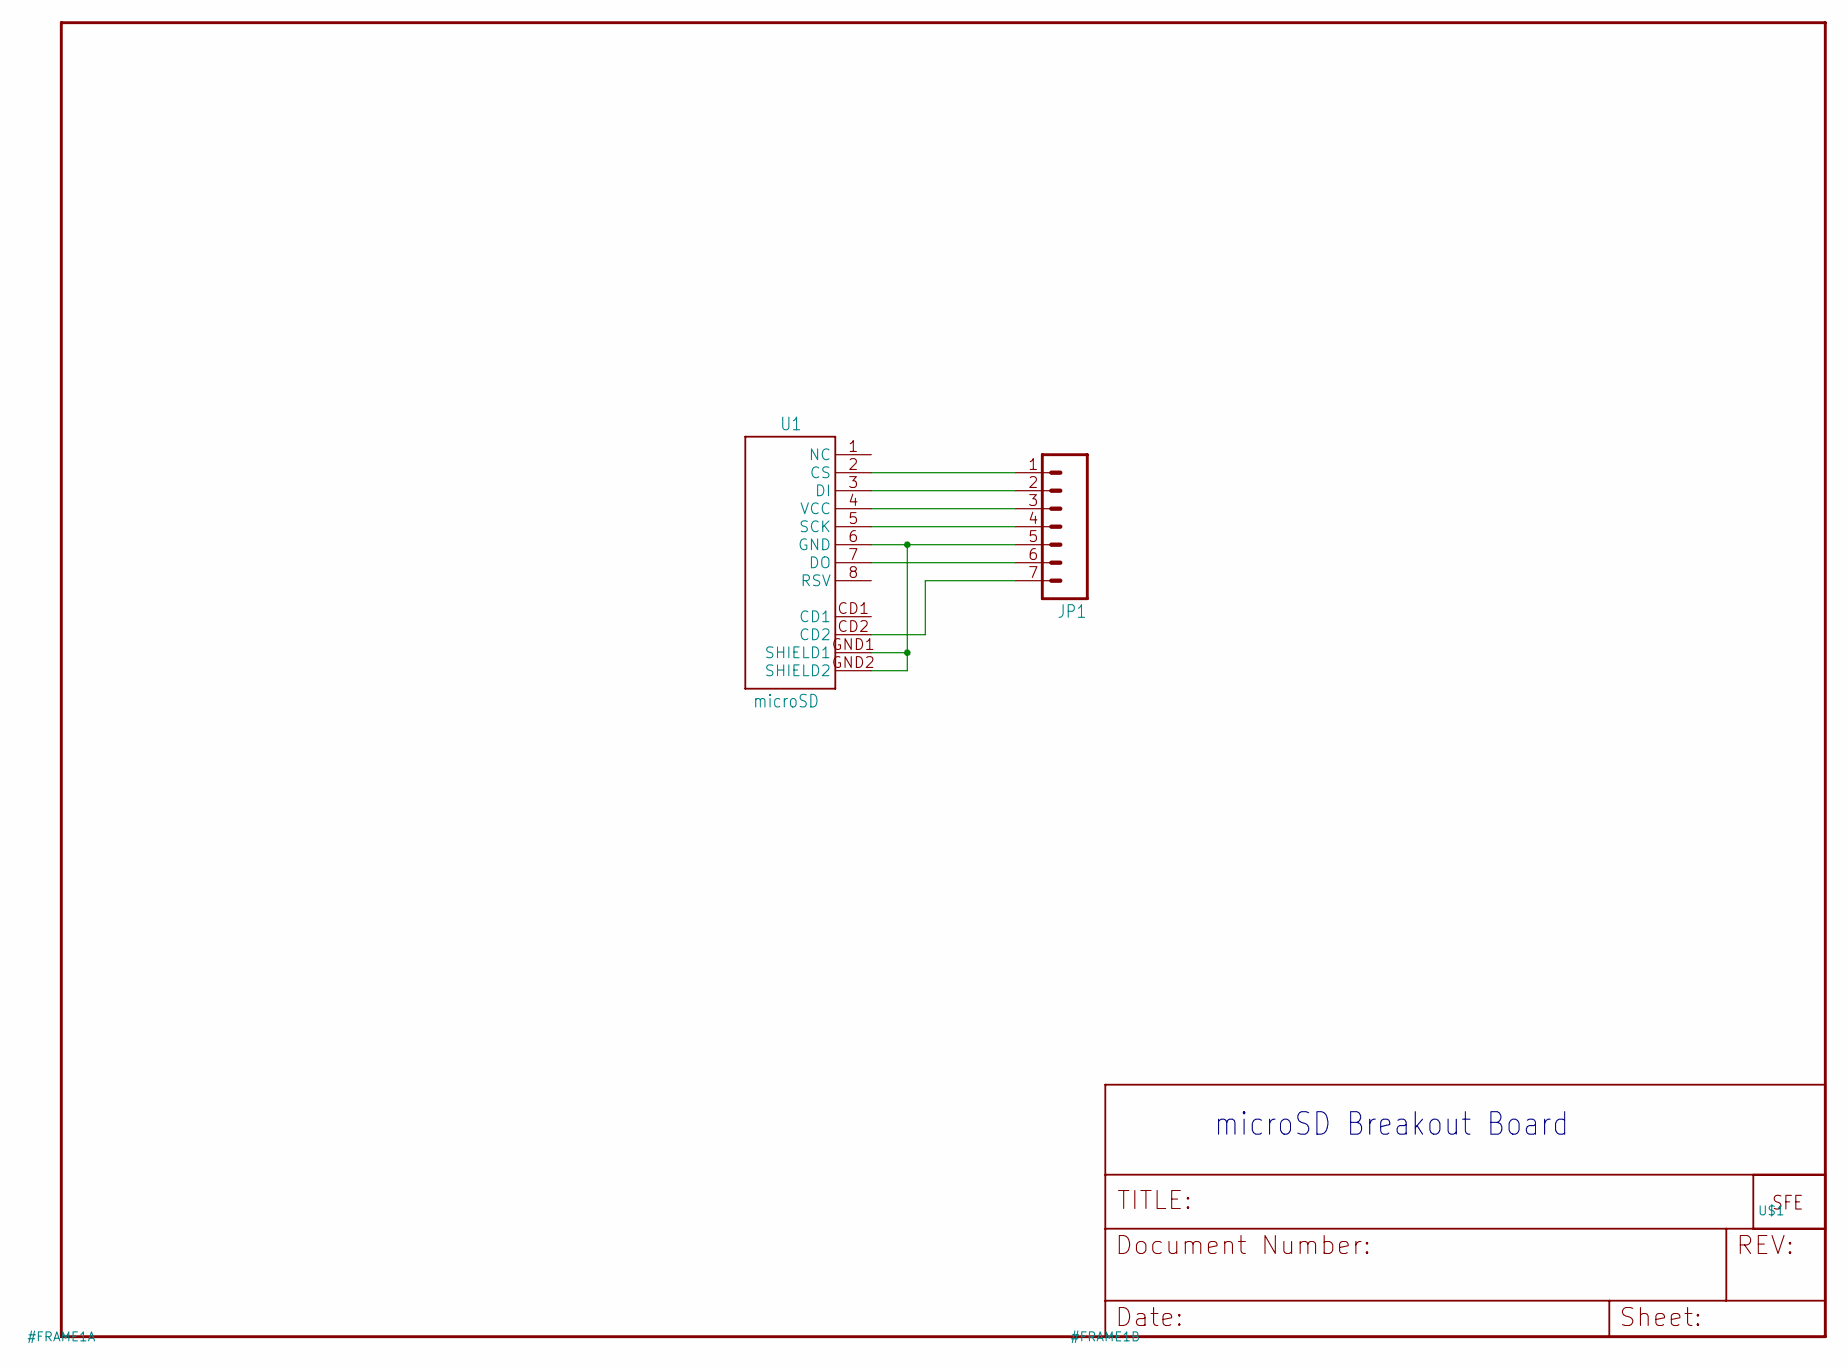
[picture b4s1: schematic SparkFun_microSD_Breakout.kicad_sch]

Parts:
JP1: M07; 1X07
U1: microSD; MICRO-SD-SOCKET-PP
U$1: LOGO-SFENEW; SFE-NEW-WEBLOGO

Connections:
CD1: JP1.7, U1.CD2
CS: JP1.1, U1.2 (CS)
DI: JP1.2, U1.3 (DI)
DO: JP1.6, U1.7 (DO)
GND: JP1.5, U1.6 (GND), U1.GND1 (SHIELD1), U1.GND2 (SHIELD2)
SCK: JP1.4, U1.5 (SCK)
VCC: JP1.3, U1.4 (VCC)

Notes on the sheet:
microSD Breakout Board

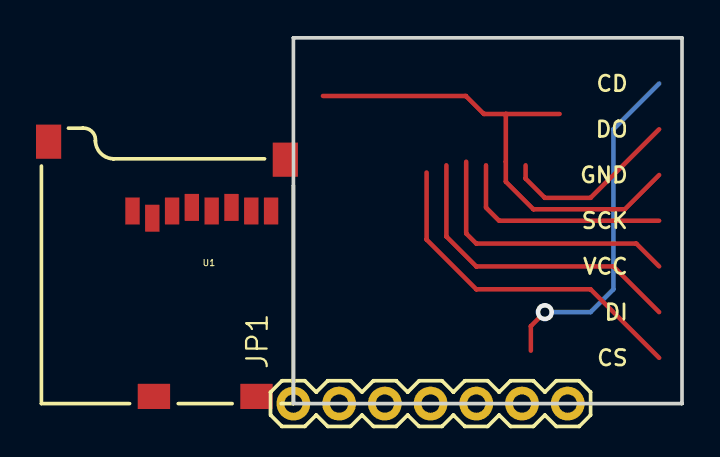
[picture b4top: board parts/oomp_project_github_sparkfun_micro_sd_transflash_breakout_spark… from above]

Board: 2 copper layers, 21.6 x 20.3 mm, 3 parts (1 on the bottom side), 7 nets.

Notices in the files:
parts/oomp_project_github_sparkfun_micro_mod_teensy_processor_micro_mod_teensy_lockable_current/data/original/kicad_file.kicad_sch:
Released under the Creative Commons
https://creativecommons.org/licenses/by-sa/4.0
parts and their libraries:
Released under the Creative Commons Attribution Share-Alike 4.0 License
